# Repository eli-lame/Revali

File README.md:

# Revali

Flight controller firmware for a **hopcopter** — a quadrotor with a passive
spring-loaded telescopic leg that lets it hop along the ground instead of
flying continuously. Hopping is dramatically more power-efficient than hover,
because thrust is applied in short bursts at launch rather than held constantly.

The design replicates the Hopcopter described in *Science Robotics* (City
University of Hong Kong / HKUST): the leg is entirely passive — rubber bands
and a sliding rod — and **all** control authority comes from the four rotors.
The firmware's job is to keep the vehicle upright and steer it by tilting,
whether it is hovering, ballistic, or compressing on the ground.

## Hardware

| Role | Part |
|---|---|
| Vehicle MCU | ESP32-WROOM |
| IMU | SparkFun ICM-20948 (accel + gyro + mag) |
| Height / ground contact | 2× VL53L0X ToF, both downward-facing, spaced apart |
| Propulsion | 4× brushless motors + ESCs, quad-X layout |
| Controller MCU | ESP32-WROOM (offboard, USB-powered from the laptop) |
| Input (reference) | 1× SparkFun analog joystick (VCC, XOUT, YOUT, SEL, GND) |
| Input (optional) | DS4 / SCUF gamepad paired to the offboard ESP32 (Bluepad32) |
| Link | ESP-NOW |
| Ground station | Browser dashboard, fed over the controller's USB cable |

The controller sends **intent** — desired roll / pitch / yaw-rate / climb-rate
— never raw throttle; altitude and hop energy are managed onboard, and the
vehicle clamps every command to its own limits. Because the wire packet carries
intent, the vehicle is **controller-agnostic**: the reference one-stick joystick
(which cycles what its two axes mean) and an optional two-stick DS4/SCUF gamepad
(which needs no cycling) feed the identical packet. See
[flight_modes.md](docs/flight_modes.md) and
[communication.md](docs/communication.md).

## Repository layout

```
firmware/     PlatformIO project — vehicle (flight controller)
controller/   PlatformIO project — offboard transmitter
shared/       Link protocol definitions included by both projects
groundstation/ Host bridge + browser dashboard
docs/         Design documents
tools/        Host-side scripts (log decoding, PID tuning, plotting)
```

## Documentation

Start with [architecture.md](docs/architecture.md), then
[hardware.md](docs/hardware.md).

| Doc | Covers |
|---|---|
| [architecture.md](docs/architecture.md) | Module boundaries and data flow |
| [hardware.md](docs/hardware.md) | Wiring, buses, pin map, the VL53L0X address problem |
| [hardware_roadmap.md](docs/hardware_roadmap.md) | Board architecture, the 4-in-1 stack, staged path to a custom FC |
| [data_model.md](docs/data_model.md) | The structs every module shares |
| [estimator.md](docs/estimator.md) | Attitude fusion and dual-ToF height |
| [control_loop.md](docs/control_loop.md) | Controller, mixer, motor output |
| [flight_modes.md](docs/flight_modes.md) | State machine; per-controller intent resolution |
| [hop_mode.md](docs/hop_mode.md) | Hop phase machine and thrust profile |
| [communication.md](docs/communication.md) | ESP-NOW link, packet format, failsafe |
| [ground_station.md](docs/ground_station.md) | Browser dashboard for live telemetry and health |
| [safety.md](docs/safety.md) | Every failsafe and its trip condition |
| [scheduler.md](docs/scheduler.md) | Task rates and timing budget |
| [current_devtasks.md](docs/current_devtasks.md) | **The build order — start here to work** |

## Status

Early. The shared data contracts and estimator interfaces exist and compile;
no driver, controller, or link is implemented yet. See
[current_devtasks.md](docs/current_devtasks.md).

## Building

```bash
cd firmware && pio run -t upload && pio device monitor
```

## License

See [LICENSE](LICENSE).

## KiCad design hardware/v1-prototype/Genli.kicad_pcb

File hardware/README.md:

# Hardware

KiCad projects for the vehicle's electronics. Design rationale lives in
[docs/hardware_roadmap.md](../docs/hardware_roadmap.md); the pin map is
authoritative in [docs/hardware.md](../docs/hardware.md).

The boards live here rather than in a separate repository because the board and
the firmware have to version together. When a GPIO moves, the schematic and
`firmware/include/board/pins.h` change in the same commit — split across two
repositories there is no way to tell, later, which board a given firmware
commit was built for.

## Layout

```
hardware/
  lib/                            symbols and footprints shared by every board
    HopCopter.pretty/               our own footprints
    Genli.kicad_sym                 our own symbols
    ESP32_Footprints.pretty/        third party, MIT
    esp32_30pin_revised.kicad_sym   third party, MIT
    ESP32-DevKit-V1-DOIT.LICENSE    its licence — keep it with the files
  v1-prototype/                   first board — archived, never fabricated
  stage2-carrier/                 current work — see its README for the spec
```

## Libraries are vendored, not installed

Every custom or third-party symbol and footprint lives in `hardware/lib/` and
is registered **per project**, never globally. A globally installed library is
invisible to the repository: the project opens on the machine that installed it
and nowhere else. v1 had exactly this problem — its symbols were referenced by
an absolute path into `OneDrive/Documents/`, so a clone of its repo could not
resolve them.

Register in *Preferences → Manage Symbol / Footprint Libraries → Project
Specific Libraries*, always with `${KIPRJMOD}`-relative paths:

| Nickname | Path |
|---|---|
| `HopCopter` | `${KIPRJMOD}/../lib/HopCopter.pretty` |
| `ESP32_Footprints` | `${KIPRJMOD}/../lib/ESP32_Footprints.pretty` |
| `Genli` | `${KIPRJMOD}/../lib/Genli.kicad_sym` |
| `esp32_30pin_revised` | `${KIPRJMOD}/../lib/esp32_30pin_revised.kicad_sym` |

**The nicknames are load-bearing — do not rename them.** Symbol and footprint
assignments are stored as `Nickname:Name`, so a nickname is a hard reference
across every sheet and every board that uses it. `HopCopter` and `Genli` are
leftovers from earlier names for this project; renaming them would break every
existing assignment for no benefit. Moving the *files* is safe; renaming the
nickname is not.

If a nickname is also registered in your global table, remove the global entry
— duplicate nicknames across the two tables produce conflicts.

The ESP32 devkit symbol and footprint are third-party
([ESP32-DevKit-V1-DOIT](https://github.com/asyaugi/ESP32-DevKit-V1-DOIT), MIT).
Its licence file sits beside them and stays there.

### Known gap

v1's PCB also references `PCM_SparkFun-Connector:ScrewTerminal_1x02_P5.0mm`,
which comes from a library installed through KiCad's Plugin and Content
Manager and is **not** vendored here. v1 is archived and that screw terminal is
deleted in Stage 2, so this is recorded rather than fixed. Do not introduce new
PCM dependencies in Stage 2 — vendor anything that isn't a KiCad stock library.

## Board naming and archives

Each board gets its own directory. Superseded boards stay, unmodified, as a
record — [hardware_roadmap.md](../docs/hardware_roadmap.md) documents v1's
defects, and that section means nothing without the schematic it refers to.

`v1-prototype/` is a snapshot. Its commit history lives in its original
repository, [eli-lame/Genli](https://github.com/eli-lame/Genli), which stays
frozen; the copy here exists so the board is visible beside the firmware it was
designed for. It keeps its original `Genli` file names — the directory name
carries the meaning, and renaming a KiCad project is the riskiest operation
available for no gain on a board that will never be edited again.

A new board is a **new KiCad project**, not a copy of the previous one. Copying
inherits the previous netlist, and v1's netlist contains the reversed
`ESC1`–`ESC4` mapping and a power section built around a part that is no longer
used. Footprints are worth reusing; net topology is not.

## Moving a KiCad project without breaking it

The rule is one change at a time, verified by opening the project between each.

1. **Copy**, do not move, the project into place. Keep the original until the
   copy is confirmed working.
2. Open it in KiCad. Confirm the schematic and the board both load, and that
   footprints resolve — the PCB editor lists unresolved ones loudly.
3. Commit that, unchanged.
4. *Then* move the `.pretty` folder to `hardware/lib/` and repoint the library
   path as above. Reopen, confirm footprints still resolve, commit.
5. Only then delete the original.

A KiCad project is `<name>.kicad_pro`, `<name>.kicad_sch` and
`<name>.kicad_pcb`, and **the root schematic must share the project's base
name**. So renaming a project means renaming all three consistently — use
*File → Save As*, which does it correctly, rather than renaming files by hand.
There is no need to rename an archived board; the directory name carries the
meaning.

## What is not committed

The root `.gitignore` excludes KiCad's per-user and regenerable files:
`*-backups/`, `*.kicad_prl`, `fp-info-cache`, `*.net`, autosave files, and
`.history/` from the VS Code local-history extension. Everything else in a
project directory is source and belongs in the repository.

Fabrication outputs (gerbers, drill files, BOM, pick-and-place) go in a
`production/` subdirectory of the board they belong to, and **are** committed —
they are the exact bytes sent to the fab, which is worth being able to
reproduce.

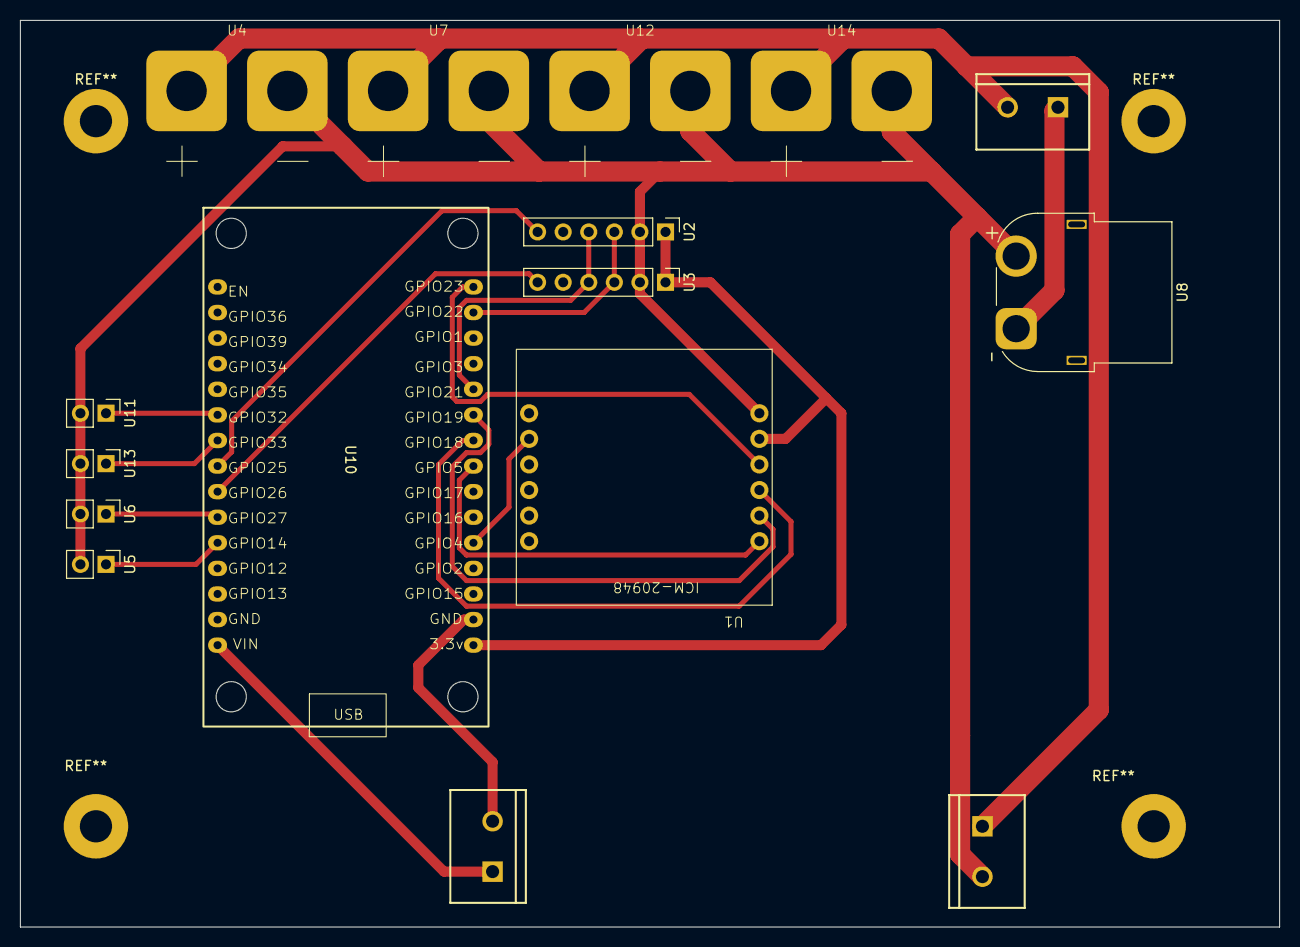
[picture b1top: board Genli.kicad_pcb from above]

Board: 2 copper layers, 125.0 x 90.0 mm, 16 parts (0 on the bottom side), 19 nets.

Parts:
J1: Screw_Terminal_01x02; ScrewTerminal_1x02_P5.0mm
U1: ICM-20948; SEN-15335
U2, U3: VL53L0X; PinHeader_1x06_P2.54mm_Vertical
U4, U7, U12, U14: ESC_Power_SolderPads_1x02
U5, U6, U11, U13: PinHeader_1x02_P2.54mm_Vertical
U8: AMASS_XT60PW-F_1x02_P7.20mm_Horizontal
U9, U15: ScrewTerminal_1x02_P5.0mm
U10: ESP32_30pin

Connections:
/ESC1_SIG: U5.1 (SIGNAL), U10.5 (GPIO14)
/ESC2_SIG: U6.1 (SIGNAL), U10.6 (GPIO27)
/ESC3_SIG: U10.9 (GPIO33), U13.1 (SIGNAL)
/ESC4_SIG: U10.10 (GPIO32), U11.1 (SIGNAL)
/ESP_3.3V: U1.5 (VIN), U2.1 (VCC), U3.1 (VCC), U10.16 (3.3v)
/GND: U1.6 (GND), U2.2 (GND), U3.2 (GND), U4.2 (BAT-), U5.2 (GND), U6.2 (GND), U7.2 (BAT-), U8.2 (BAT-), U9.2 (VIN-), U11.2 (GND), U12.2 (BAT-), U13.2 (GND), U14.2 (BAT-)
/I2C_SCL: U2.3 (SCL), U3.3 (SCL), U10.29 (GPIO22)
/I2C_SDA: U2.4 (SDA), U3.4 (SDA), U10.26 (GPIO21)
/IMU_CS: U1.1 (CS), U10.23 (GPIO5)
/IMU_INT: U1.11 (INT), U10.20 (GPIO4)
/IMU_MISO: U1.2 (MISO), U10.25 (GPIO19)
/IMU_MOSI: U1.4 (MOSI), U10.30 (GPIO23)
/IMU_SCLK: U1.3 (SCLK), U10.24 (GPIO18)
/TOF1_XSHUT: U2.6 (XSHUT), U10.8 (GPIO25)
/TOF2_XSHUT: U3.6 (XSHUT), U10.7 (GPIO26)
/VBAT: J1.2, U4.1 (BAT+), U7.1 (BAT+), U9.1 (VIN+), U12.1 (BAT+), U14.1 (BAT+)
unnamed: J1.1, U8.1 (BAT+)
unnamed: U10.1 (VIN), U15.1 (5V)
unnamed: U10.17 (GND), U15.2 (GND)
